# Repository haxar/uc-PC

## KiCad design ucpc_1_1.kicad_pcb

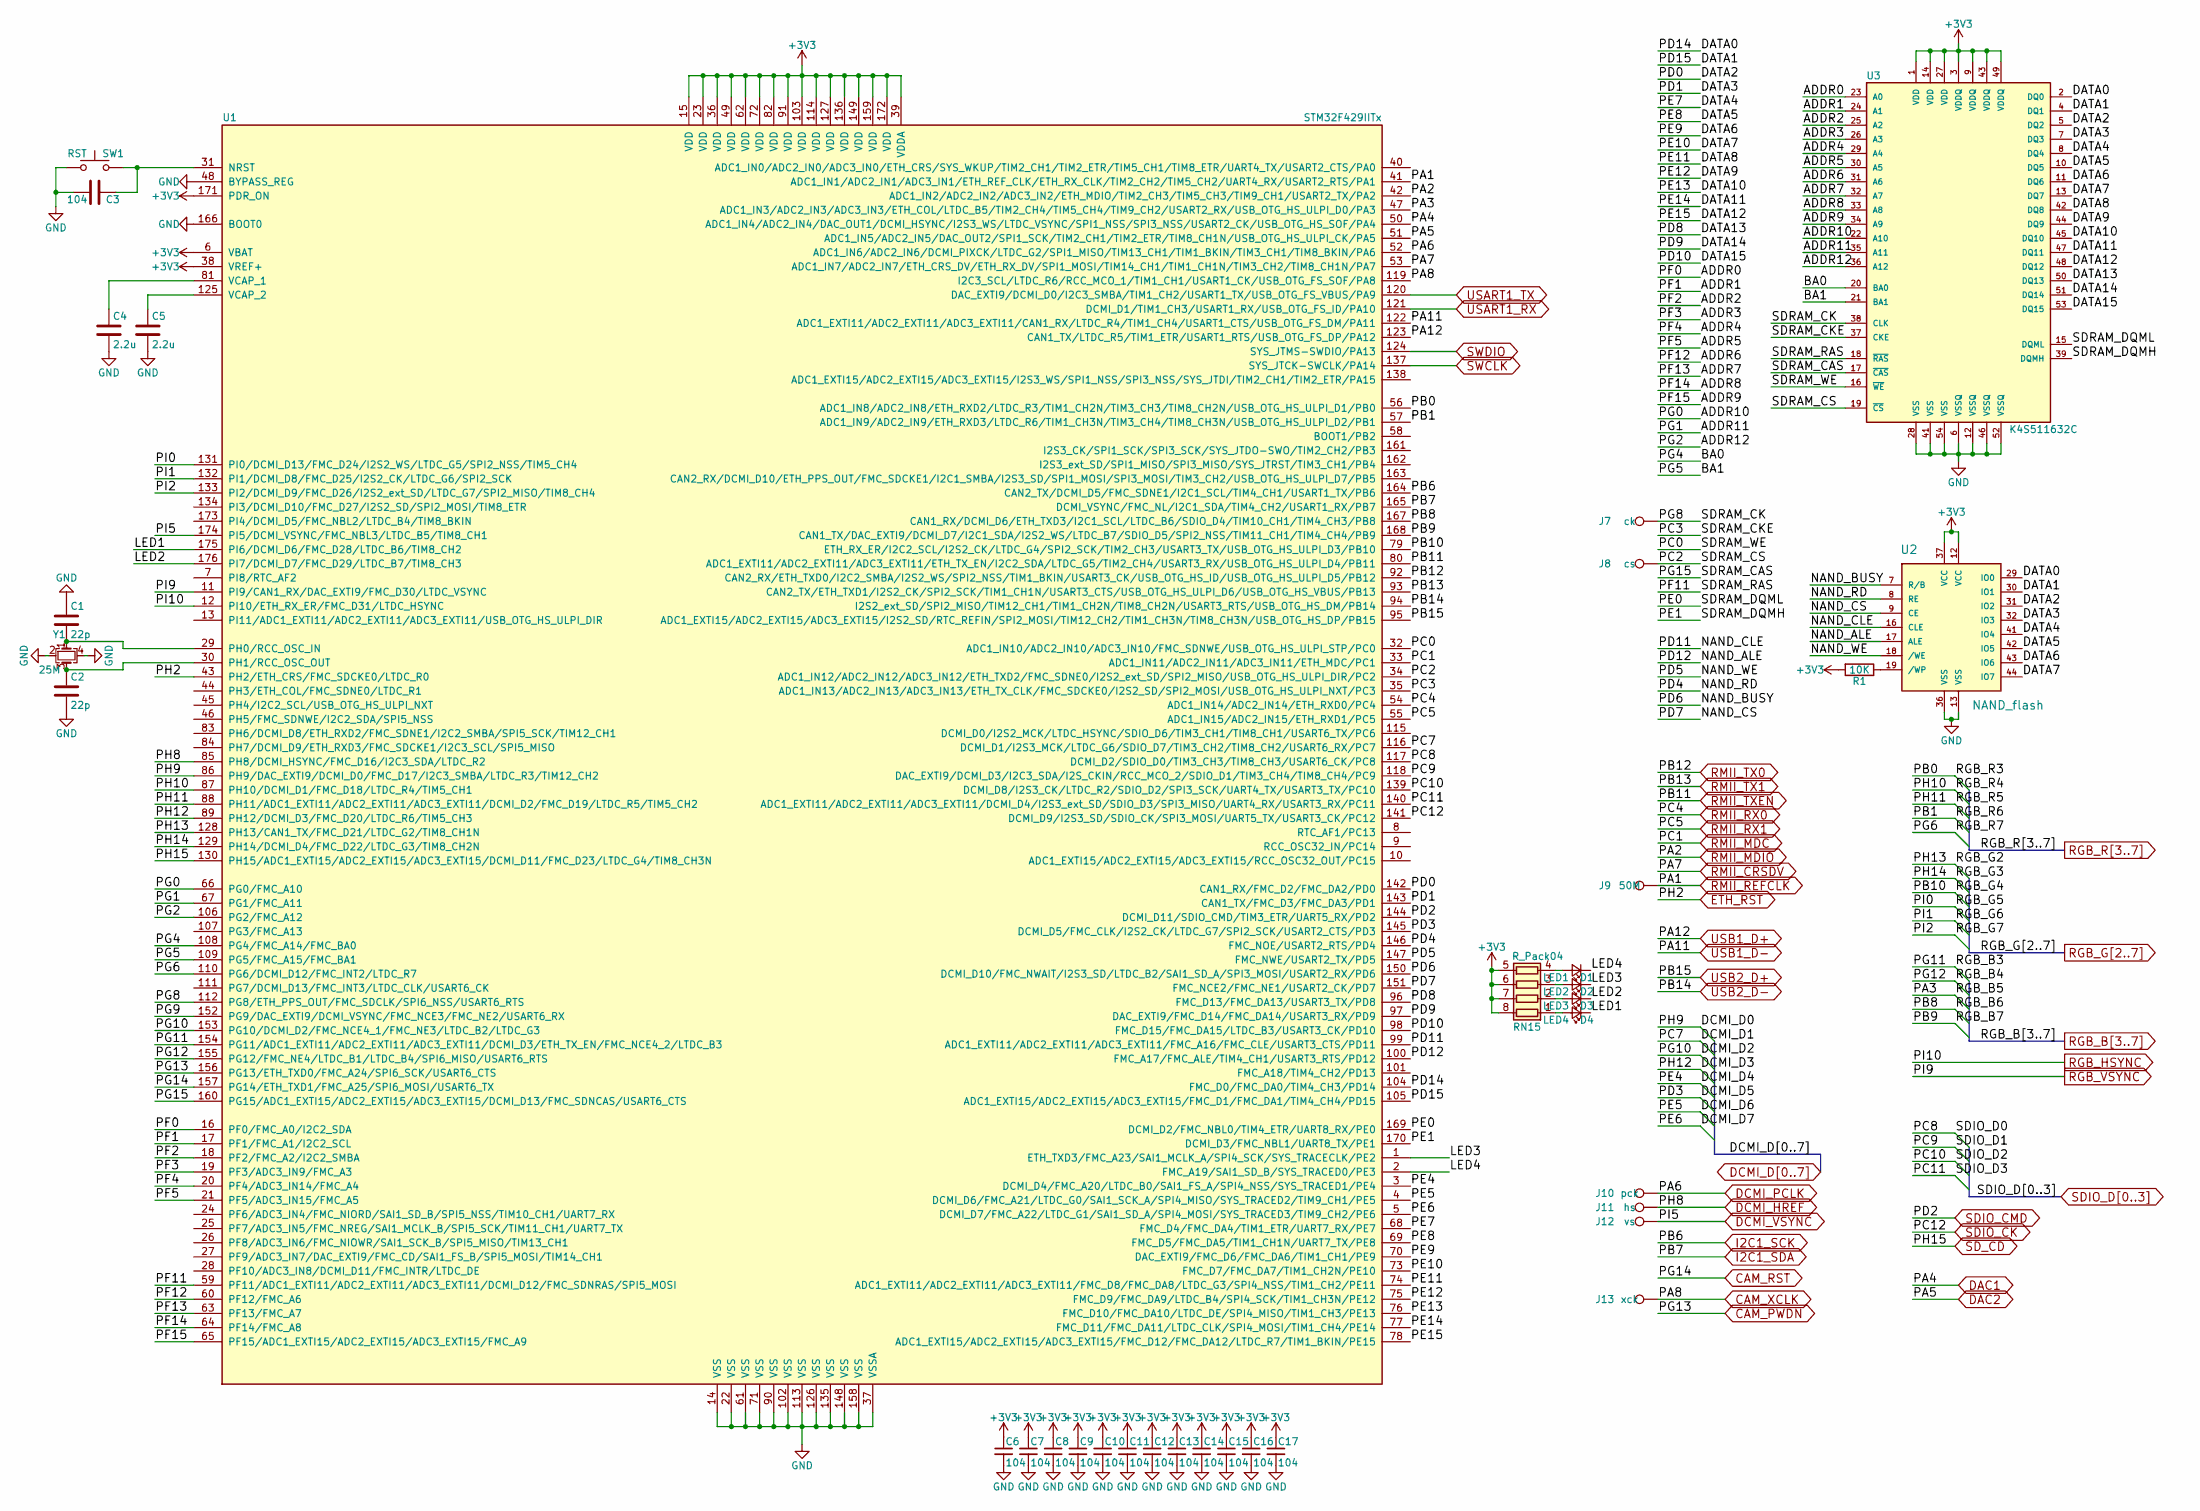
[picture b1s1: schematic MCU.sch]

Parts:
C1, C2: 22p; C_0603_1608Metric_Pad0.84x1.00mm_HandSolder
C3, C6, C7, C8, C9, C10, C11, C12, C13, C14, C15, C16, C17: 104; C_0603_1608Metric_Pad0.84x1.00mm_HandSolder
C4, C5: 2.2u; C_0603_1608Metric_Pad0.84x1.00mm_HandSolder
D1: LED1; D_0603_1608Metric_Pad0.67x1.00mm_HandSolder
D2: LED2; D_0603_1608Metric_Pad0.67x1.00mm_HandSolder
D3: LED3; D_0603_1608Metric_Pad0.67x1.00mm_HandSolder
D4: LED4; D_0603_1608Metric_Pad0.67x1.00mm_HandSolder
J7: ck; testpoint
J8: cs; testpoint
J9: 50M; testpoint
J10: pck; testpoint
J11: hs; testpoint
J12: vs; testpoint
J13: xck; testpoint
R1: 10K; R_0603_1608Metric_Pad0.84x1.00mm_HandSolder
RN15: R_Pack04; R_Array_Convex_4x0603
SW1: RST; SW_DIP_SPSTx01_Slide_6.7x4.1mm_W6.73mm_P2.54mm_LowProfile_J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
U1: STM32F429IITx; LQFP-176_24x24mm_Pitch0.5mm
U2: NAND_flash; TSSOP48
U3: K4S511632C; TSOP-54-0.8-pitch
Y1: 25M; Crystal_SMD_3225-4Pin_3.2x2.5mm

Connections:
+3V3: C6.1, C7.1, C8.1, C9.1, C10.1, C11.1, C12.1, C13.1, C14.1, C15.1, C16.1, C17.1, R1.2, RN15.5 (R4.2), RN15.6 (R3.2), RN15.7 (R2.2), RN15.8 (R1.2), U1.6 (VBAT), U1.15 (VDD), U1.23 (VDD), U1.36 (VDD), U1.38 (VREF+), U1.39 (VDDA), U1.49 (VDD), U1.62 (VDD), U1.72 (VDD), U1.82 (VDD), U1.91 (VDD), U1.103 (VDD), U1.114 (VDD), U1.127 (VDD), U1.136 (VDD), U1.149 (VDD), U1.159 (VDD), U1.171 (PDR_ON), U1.172 (VDD), U2.12 (VCC), U2.37 (VCC), U3.1 (VDD), U3.3 (VDDQ), U3.9 (VDDQ), U3.14 (VDD), U3.27 (VDD), U3.43 (VDDQ), U3.49 (VDDQ); also elsewhere on the board
/stm32f429iit6/ADDR0: U1.16 (PF0/FMC_A0/I2C2_SDA), U3.23 (A0)
/stm32f429iit6/ADDR1: U1.17 (PF1/FMC_A1/I2C2_SCL), U3.24 (A1)
/stm32f429iit6/ADDR2: U1.18 (PF2/FMC_A2/I2C2_SMBA), U3.25 (A2)
/stm32f429iit6/ADDR3: U1.19 (PF3/ADC3_IN9/FMC_A3), U3.26 (A3)
/stm32f429iit6/ADDR4: U1.20 (PF4/ADC3_IN14/FMC_A4), U3.29 (A4)
/stm32f429iit6/ADDR5: U1.21 (PF5/ADC3_IN15/FMC_A5), U3.30 (A5)
/stm32f429iit6/ADDR6: U1.60 (PF12/FMC_A6), U3.31 (A6)
/stm32f429iit6/ADDR7: U1.63 (PF13/FMC_A7), U3.32 (A7)
/stm32f429iit6/ADDR8: U1.64 (PF14/FMC_A8), U3.33 (A8)
/stm32f429iit6/ADDR9: U1.65 (PF15/ADC1_EXTI15/ADC2_EXTI15/ADC3_EXTI1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), U3.34 (A9)
/stm32f429iit6/ADDR10: U1.66 (PG0/FMC_A10), U3.22 (A10)
/stm32f429iit6/ADDR11: U1.67 (PG1/FMC_A11), U3.35 (A11)
/stm32f429iit6/ADDR12: U1.106 (PG2/FMC_A12), U3.36 (A12)
/stm32f429iit6/BA0: U1.108 (PG4/FMC_A14/FMC_BA0), U3.20 (BA0)
/stm32f429iit6/BA1: U1.109 (PG5/FMC_A15/FMC_BA1), U3.21 (BA1)
/stm32f429iit6/DATA0: U1.104 (FMC_D0/FMC_DA0/TIM4_CH3/PD14), U2.29 (IO0), U3.2 (DQ0)
/stm32f429iit6/DATA1: U1.105 (ADC1_EXTI15/ADC2_EXTI15/ADC3_EXTI15/FMC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), U2.30 (IO1), U3.4 (DQ1)
/stm32f429iit6/DATA2: U1.142 (CAN1_RX/FMC_D2/FMC_DA2/PD0), U2.31 (IO2), U3.5 (DQ2)
/stm32f429iit6/DATA3: U1.143 (CAN1_TX/FMC_D3/FMC_DA3/PD1), U2.32 (IO3), U3.7 (DQ3)
/stm32f429iit6/DATA4: U1.68 (FMC_D4/FMC_DA4/TIM1_ETR/UART7_RX/PE7), U2.41 (IO4), U3.8 (DQ4)
/stm32f429iit6/DATA5: U1.69 (FMC_D5/FMC_DA5/TIM1_CH1N/UART7_TX/PE8), U2.42 (IO5), U3.10 (DQ5)
/stm32f429iit6/DATA6: U1.70 (DAC_EXTI9/FMC_D6/FMC_DA6/TIM1_CH1/PE9), U2.43 (IO6), U3.11 (DQ6)
/stm32f429iit6/DATA7: U1.73 (FMC_D7/FMC_DA7/TIM1_CH2N/PE10), U2.44 (IO7), U3.13 (DQ7)
/stm32f429iit6/DATA8: U1.74 (ADC1_EXTI11/ADC2_EXTI11/ADC3_EXTI11/FMC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), U3.42 (DQ8)
/stm32f429iit6/DATA9: U1.75 (FMC_D9/FMC_DA9/LTDC_B4/SPI4_SCK/TIM1_CH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), U3.44 (DQ9)
/stm32f429iit6/DATA10: U1.76 (FMC_D10/FMC_DA10/LTDC_DE/SPI4_MISO/TIM1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), U3.45 (DQ10)
/stm32f429iit6/DATA11: U1.77 (FMC_D11/FMC_DA11/LTDC_CLK/SPI4_MOSI/TIM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), U3.47 (DQ11)
/stm32f429iit6/DATA12: U1.78 (ADC1_EXTI15/ADC2_EXTI15/ADC3_EXTI15/FMC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), U3.48 (DQ12)
/stm32f429iit6/DATA13: U1.96 (FMC_D13/FMC_DA13/USART3_TX/PD8), U3.50 (DQ13)
/stm32f429iit6/DATA14: U1.97 (DAC_EXTI9/FMC_D14/FMC_DA14/USART3_RX/PD9), U3.51 (DQ14)
/stm32f429iit6/DATA15: U1.98 (FMC_D15/FMC_DA15/LTDC_B3/USART3_CK/PD10), U3.53 (DQ15)
/stm32f429iit6/LED1: D4.1 (K), U1.175 (PI6/DCMI_D6/FMC_D28/LTDC_B6/TIM8_CH2)
/stm32f429iit6/LED2: D3.1 (K), U1.176 (PI7/DCMI_D7/FMC_D29/LTDC_B7/TIM8_CH3)
/stm32f429iit6/LED3: D2.1 (K), U1.1 (ETH_TXD3/FMC_A23/SAI1_MCLK_A/SPI4_SCK/S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)
/stm32f429iit6/LED4: D1.1 (K), U1.2 (FMC_A19/SAI1_SD_B/SYS_TRACED0/PE3)
/stm32f429iit6/NAND_ALE: U1.100 (FMC_A17/FMC_ALE/TIM4_CH1/USART3_RTS/PD12), U2.17 (ALE)
/stm32f429iit6/NAND_BUSY: U1.150 (DCMI_D10/FMC_NWAIT/I2S3_SD/LTDC_B2/SAI1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), U2.7 (R/B)
/stm32f429iit6/NAND_CLE: U1.99 (ADC1_EXTI11/ADC2_EXTI11/ADC3_EXTI11/FMC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), U2.16 (CLE)
/stm32f429iit6/NAND_CS: U1.151 (FMC_NCE2/FMC_NE1/USART2_CK/PD7), U2.9 (CE)
/stm32f429iit6/NAND_RD: U1.146 (FMC_NOE/USART2_RTS/PD4), U2.8 (RE)
/stm32f429iit6/NAND_WE: U1.147 (FMC_NWE/USART2_TX/PD5), U2.18 (/WE)
/stm32f429iit6/PC0: U1.32 (ADC1_IN10/ADC2_IN10/ADC3_IN10/FMC_SDNWE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), U3.16 (~WE~)
/stm32f429iit6/PC2: J8.1, U1.34 (ADC1_IN12/ADC2_IN12/ADC3_IN12/ETH_TXD2/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), U3.19 (~CS~)
/stm32f429iit6/PC3: U1.35 (ADC1_IN13/ADC2_IN13/ADC3_IN13/ETH_TX_CL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), U3.37 (CKE)
/stm32f429iit6/PE0: U1.169 (DCMI_D2/FMC_NBL0/TIM4_ETR/UART8_RX/PE0), U3.15 (DQML)
/stm32f429iit6/PE1: U1.170 (DCMI_D3/FMC_NBL1/UART8_TX/PE1), U3.39 (DQMH)
/stm32f429iit6/PF11: U1.59 (PF11/ADC1_EXTI11/ADC2_EXTI11/ADC3_EXTI1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), U3.18 (~RAS~)
/stm32f429iit6/PG8: J7.1, U1.112 (PG8/ETH_PPS_OUT/FMC_SDCLK/SPI6_NSS/USAR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), U3.38 (CLK)
/stm32f429iit6/PG9: U1.152 (PG9/DAC_EXTI9/DCMI_VSYNC/FMC_NCE3/FMC_N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)
/stm32f429iit6/PG15: U1.160 (PG15/ADC1_EXTI15/ADC2_EXTI15/ADC3_EXTI1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), U3.17 (~CAS~)
CAM_PWDN: U1.156 (PG13/ETH_TXD0/FMC_A24/SPI6_SCK/USART6_C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); also elsewhere on the board
CAM_RST: U1.157 (PG14/ETH_TXD1/FMC_A25/SPI6_MOSI/USART6_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); also elsewhere on the board
CAM_XCLK: J13.1, U1.119 (I2C3_SCL/LTDC_R6/RCC_MCO_1/TIM1_CH1/USA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); also elsewhere on the board
DAC1: U1.50 (ADC1_IN4/ADC2_IN4/DAC_OUT1/DCMI_HSYNC/I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); also elsewhere on the board
DAC2: U1.51 (ADC1_IN5/ADC2_IN5/DAC_OUT2/SPI1_SCK/TIM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); also elsewhere on the board
DCMI_D0: U1.86 (PH9/DAC_EXTI9/DCMI_D0/FMC_D17/I2C3_SMBA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); also elsewhere on the board
DCMI_D1: U1.116 (DCMI_D1/I2S3_MCK/LTDC_G6/SDIO_D7/TIM3_C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); also elsewhere on the board
DCMI_D2: U1.153 (PG10/DCMI_D2/FMC_NCE4_1/FMC_NE3/LTDC_B2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); also elsewhere on the board
DCMI_D3: U1.89 (PH12/DCMI_D3/FMC_D20/LTDC_R6/TIM5_CH3); also elsewhere on the board
DCMI_D4: U1.3 (DCMI_D4/FMC_A20/LTDC_B0/SAI1_FS_A/SPI4_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); also elsewhere on the board
DCMI_D5: U1.145 (DCMI_D5/FMC_CLK/I2S2_CK/LTDC_G7/SPI2_SC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); also elsewhere on the board
DCMI_D6: U1.4 (DCMI_D6/FMC_A21/LTDC_G0/SAI1_SCK_A/SPI4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); also elsewhere on the board
DCMI_D7: U1.5 (DCMI_D7/FMC_A22/LTDC_G1/SAI1_SD_A/SPI4_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); also elsewhere on the board
DCMI_HREF: J11.1, U1.85 (PH8/DCMI_HSYNC/FMC_D16/I2C3_SDA/LTDC_R2); also elsewhere on the board
DCMI_PCLK: J10.1, U1.52 (ADC1_IN6/ADC2_IN6/DCMI_PIXCK/LTDC_G2/SP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); also elsewhere on the board
DCMI_VSYNC: J12.1, U1.174 (PI5/DCMI_VSYNC/FMC_NBL3/LTDC_B5/TIM8_CH1); also elsewhere on the board
ETH_RST: U1.43 (PH2/ETH_CRS/FMC_SDCKE0/LTDC_R0); also elsewhere on the board
GND: C1.1, C2.2, C3.2, C4.2, C5.2, C6.2, C7.2, C8.2, C9.2, C10.2, C11.2, C12.2, C13.2, C14.2, C15.2, C16.2, C17.2, SW1.1, U1.14 (VSS), U1.22 (VSS), U1.37 (VSSA), U1.48 (BYPASS_REG), U1.61 (VSS), U1.71 (VSS), U1.90 (VSS), U1.102 (VSS), U1.113 (VSS), U1.126 (VSS), U1.135 (VSS), U1.148 (VSS), U1.158 (VSS), U1.166 (BOOT0), U2.13 (VSS), U2.36 (VSS), U3.6 (VSSQ), U3.12 (VSSQ), U3.28 (VSS), U3.41 (VSS), U3.46 (VSSQ), U3.52 (VSSQ), U3.54 (VSS), Y1.2, Y1.4; also elsewhere on the board
I2C1_SCK: U1.164 (CAN2_TX/DCMI_D5/FMC_SDNE1/I2C1_SCL/TIM4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); also elsewhere on the board
I2C1_SDA: U1.165 (DCMI_VSYNC/FMC_NL/I2C1_SDA/TIM4_CH2/USA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); also elsewhere on the board
unnamed: C1.2, U1.29 (PH0/RCC_OSC_IN), Y1.1
unnamed: C2.1, U1.30 (PH1/RCC_OSC_OUT), Y1.3
unnamed: C3.1, SW1.2, U1.31 (NRST)
unnamed: C4.1, U1.81 (VCAP_1)
unnamed: C5.1, U1.125 (VCAP_2)
unnamed: D1.2 (A), RN15.4 (R4.1)
unnamed: D2.2 (A), RN15.3 (R3.1)
unnamed: D3.2 (A), RN15.2 (R2.1)
unnamed: D4.2 (A), RN15.1 (R1.1)
unnamed: R1.1, U2.19 (/WP)
RGB_B3: U1.154 (PG11/ADC1_EXTI11/ADC2_EXTI11/ADC3_EXTI1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); also elsewhere on the board
RGB_B4: U1.155 (PG12/FMC_NE4/LTDC_B1/LTDC_B4/SPI6_MISO/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); also elsewhere on the board
RGB_B5: U1.47 (ADC1_IN3/ADC2_IN3/ADC3_IN3/ETH_COL/LTDC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); also elsewhere on the board
RGB_B6: U1.167 (CAN1_RX/DCMI_D6/ETH_TXD3/I2C1_SCL/LTDC_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); also elsewhere on the board
RGB_B7: U1.168 (CAN1_TX/DAC_EXTI9/DCMI_D7/I2C1_SDA/I2S2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); also elsewhere on the board
RGB_G2: U1.128 (PH13/CAN1_TX/FMC_D21/LTDC_G2/TIM8_CH1N); also elsewhere on the board
RGB_G3: U1.129 (PH14/DCMI_D4/FMC_D22/LTDC_G3/TIM8_CH2N); also elsewhere on the board
RGB_G4: U1.79 (ETH_RX_ER/I2C2_SCL/I2S2_CK/LTDC_G4/SPI2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); also elsewhere on the board
RGB_G5: U1.131 (PI0/DCMI_D13/FMC_D24/I2S2_WS/LTDC_G5/SP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); also elsewhere on the board
RGB_G6: U1.132 (PI1/DCMI_D8/FMC_D25/I2S2_CK/LTDC_G6/SPI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); also elsewhere on the board
RGB_G7: U1.133 (PI2/DCMI_D9/FMC_D26/I2S2_ext_SD/LTDC_G7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); also elsewhere on the board
RGB_HSYNC: U1.12 (PI10/ETH_RX_ER/FMC_D31/LTDC_HSYNC); also elsewhere on the board
RGB_R3: U1.56 (ADC1_IN8/ADC2_IN8/ETH_RXD2/LTDC_R3/TIM1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); also elsewhere on the board
RGB_R4: U1.87 (PH10/DCMI_D1/FMC_D18/LTDC_R4/TIM5_CH1); also elsewhere on the board
RGB_R5: U1.88 (PH11/ADC1_EXTI11/ADC2_EXTI11/ADC3_EXTI1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); also elsewhere on the board
RGB_R6: U1.57 (ADC1_IN9/ADC2_IN9/ETH_RXD3/LTDC_R6/TIM1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); also elsewhere on the board
RGB_R7: U1.110 (PG6/DCMI_D12/FMC_INT2/LTDC_R7); also elsewhere on the board
RGB_VSYNC: U1.11 (PI9/CAN1_RX/DAC_EXTI9/FMC_D30/LTDC_VSYNC); also elsewhere on the board
RMII_CRSDV: U1.53 (ADC1_IN7/ADC2_IN7/ETH_CRS_DV/ETH_RX_DV/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); also elsewhere on the board
RMII_MDC: U1.33 (ADC1_IN11/ADC2_IN11/ADC3_IN11/ETH_MDC/P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); also elsewhere on the board
RMII_MDIO: U1.42 (ADC1_IN2/ADC2_IN2/ADC3_IN2/ETH_MDIO/TIM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); also elsewhere on the board
RMII_REFCLK: J9.1, U1.41 (ADC1_IN1/ADC2_IN1/ADC3_IN1/ETH_REF_CLK/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); also elsewhere on the board
RMII_RX0: U1.54 (ADC1_IN14/ADC2_IN14/ETH_RXD0/PC4); also elsewhere on the board
RMII_RX1: U1.55 (ADC1_IN15/ADC2_IN15/ETH_RXD1/PC5); also elsewhere on the board
RMII_TX0: U1.92 (CAN2_RX/ETH_TXD0/I2C2_SMBA/I2S2_WS/SPI2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); also elsewhere on the board
RMII_TX1: U1.93 (CAN2_TX/ETH_TXD1/I2S2_CK/SPI2_SCK/TIM1_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); also elsewhere on the board
RMII_TXEN: U1.80 (ADC1_EXTI11/ADC2_EXTI11/ADC3_EXTI11/ETH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); also elsewhere on the board
SDIO_CK: U1.141 (DCMI_D9/I2S3_SD/SDIO_CK/SPI3_MOSI/UART5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); also elsewhere on the board
SDIO_CMD: U1.144 (DCMI_D11/SDIO_CMD/TIM3_ETR/UART5_RX/PD2); also elsewhere on the board
SDIO_D0: U1.117 (DCMI_D2/SDIO_D0/TIM3_CH3/TIM8_CH3/USART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); also elsewhere on the board
SDIO_D1: U1.118 (DAC_EXTI9/DCMI_D3/I2C3_SDA/I2S_CKIN/RCC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); also elsewhere on the board
SDIO_D2: U1.139 (DCMI_D8/I2S3_CK/LTDC_R2/SDIO_D2/SPI3_SC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); also elsewhere on the board
SDIO_D3: U1.140 (ADC1_EXTI11/ADC2_EXTI11/ADC3_EXTI11/DCM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); also elsewhere on the board
SD_CD: U1.130 (PH15/ADC1_EXTI15/ADC2_EXTI15/ADC3_EXTI1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); also elsewhere on the board
SWCLK: U1.137 (SYS_JTCK-SWCLK/PA14); also elsewhere on the board
SWDIO: U1.124 (SYS_JTMS-SWDIO/PA13); also elsewhere on the board
USART1_RX: U1.121 (DCMI_D1/TIM1_CH3/USART1_RX/USB_OTG_FS_I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); also elsewhere on the board
USART1_TX: U1.120 (DAC_EXTI9/DCMI_D0/I2C3_SMBA/TIM1_CH2/US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); also elsewhere on the board
USB1_D+: U1.123 (CAN1_TX/LTDC_R5/TIM1_ETR/USART1_RTS/USB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); also elsewhere on the board
USB1_D-: U1.122 (ADC1_EXTI11/ADC2_EXTI11/ADC3_EXTI11/CAN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); also elsewhere on the board
USB2_D+: U1.95 (ADC1_EXTI15/ADC2_EXTI15/ADC3_EXTI15/I2S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); also elsewhere on the board
USB2_D-: U1.94 (I2S2_ext_SD/SPI2_MISO/TIM12_CH1/TIM1_CH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); also elsewhere on the board

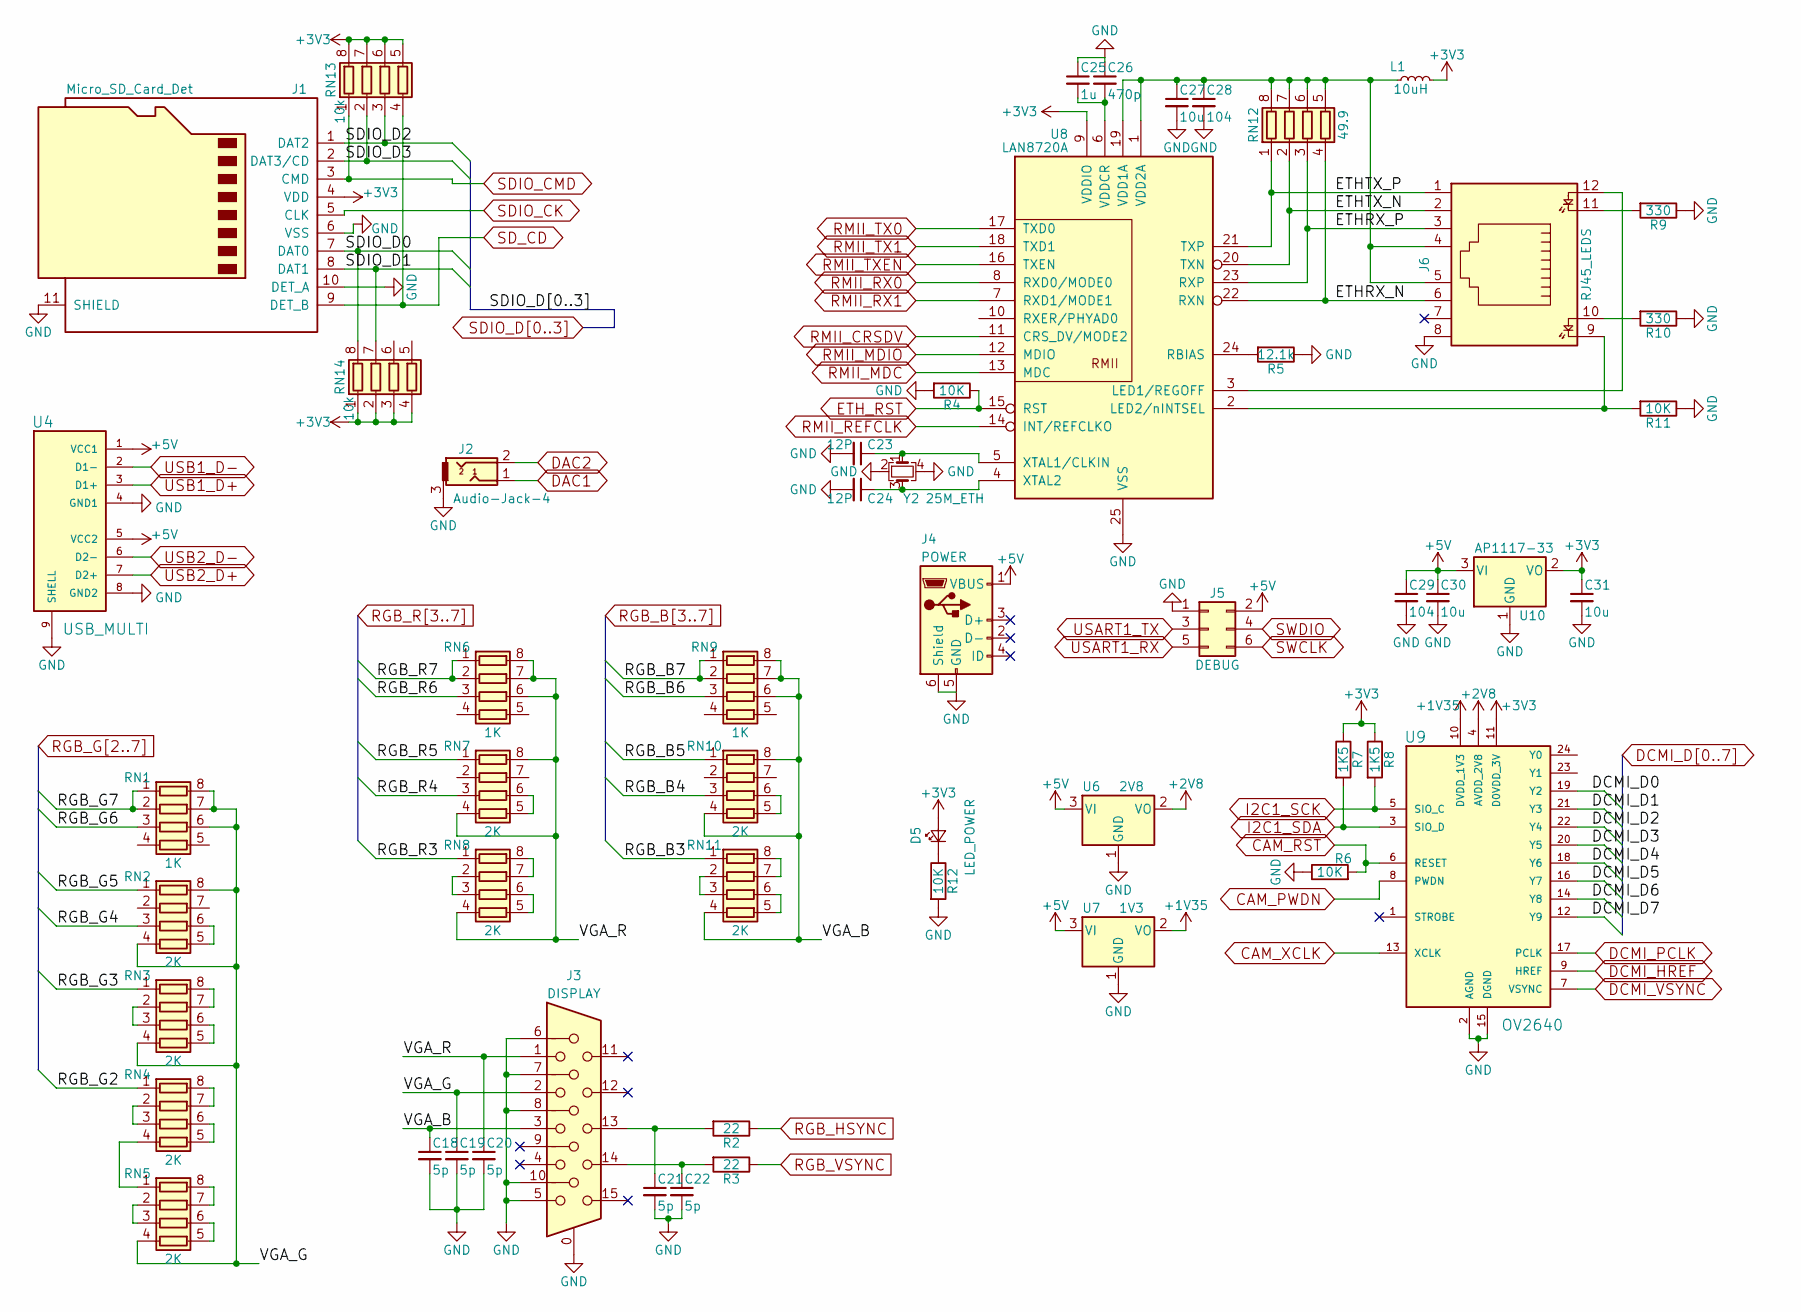
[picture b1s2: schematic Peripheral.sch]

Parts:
C18, C19, C20, C21, C22: 5p; C_0603_1608Metric_Pad0.84x1.00mm_HandSolder
C23, C24: 12P; C_0603_1608Metric_Pad0.84x1.00mm_HandSolder
C25: 1u; C_0603_1608Metric_Pad0.84x1.00mm_HandSolder
C26: 470p; C_0603_1608Metric_Pad0.84x1.00mm_HandSolder
C27: 10u; C_0603_1608Metric_Pad0.84x1.00mm_HandSolder
C28, C29: 104; C_0603_1608Metric_Pad0.84x1.00mm_HandSolder
C30, C31: 10u; C_0805_2012Metric_Pad1.15x1.50mm_HandSolder
D5: LED_POWER; D_0603_1608Metric_Pad0.67x1.00mm_HandSolder
J1: Micro_SD_Card_Det; TF_CARD_SMALL
J2: Audio-Jack-4; PJ215-3.5MM-AUDIO
J3: DISPLAY; VGA-15-3.96
J4: POWER; USB_Micro-B
J5: DEBUG; PinHeader_2x03_P2.54mm_Vertical
J6: RJ45_LEDS; HR911105A_1
L1: 10uH; L_0805_2012Metric_Pad1.15x1.50mm_HandSolder
R2, R3: 22; R_0603_1608Metric_Pad0.84x1.00mm_HandSolder
R4, R6, R11, R12: 10K; R_0603_1608Metric_Pad0.84x1.00mm_HandSolder
R5: 12.1k; R_0603_1608Metric_Pad0.84x1.00mm_HandSolder
R7, R8: 1K5; R_0603_1608Metric_Pad0.84x1.00mm_HandSolder
R9, R10: 330; R_0603_1608Metric_Pad0.84x1.00mm_HandSolder
RN1, RN6, RN9: 1K; R_Array_Convex_4x0603
RN2, RN3, RN4, RN5, RN7, RN8, RN10, RN11: 2K; R_Array_Convex_4x0603
RN12: 49.9; R_Array_Convex_4x0603
RN13, RN14: 10k; R_Array_Convex_4x0603
U4: USB_MULTI; USB_DOUBLE
U6: 2V8; SC-59_Handsoldering
U7: 1V3; SC-59_Handsoldering
U8: LAN8720A; QFN-24-1EP_4x4mm_P0.5mm_EP2.6x2.6mm
U9: OV2640; FPC-24-0.5-pitch
U10: AP1117-33; SOT-223-3_TabPin2
Y2: 25M_ETH; Crystal_SMD_3225-4Pin_3.2x2.5mm

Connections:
+1V35: U7.2 (VO), U9.10 (DVDD_1V3)
+2V8: U6.2 (VO), U9.4 (AVDD_2V8)
+3V3: C31.1, D5.2 (A), J1.4 (VDD), L1.2, R7.1, R8.1, RN13.5 (R4.2), RN13.6 (R3.2), RN13.7 (R2.2), RN13.8 (R1.2), RN14.1 (R1.1), RN14.2 (R2.1), RN14.3 (R3.1), RN14.4 (R4.1), U8.9 (VDDIO), U9.11 (D0VDD_3V), U10.2 (VO); also elsewhere on the board
+5V: C29.1, C30.1, J4.1 (VBUS), J5.2, U4.1 (VCC1), U4.5 (VCC2), U6.3 (VI), U7.3 (VI), U10.3 (VI)
/peripheral/ETHRX_N: J6.6, RN12.4 (R4.1), U8.22 (RXN)
/peripheral/ETHRX_P: J6.3, RN12.3 (R3.1), U8.23 (RXP)
/peripheral/ETHTX_N: J6.2, RN12.2 (R2.1), U8.20 (TXN)
/peripheral/ETHTX_P: J6.1, RN12.1 (R1.1), U8.21 (TXP)
/peripheral/VGA_B: C18.1, J3.3, RN9.6 (R3.2), RN9.7 (R2.2), RN9.8 (R1.2), RN10.4 (R4.1), RN10.8 (R1.2), RN11.4 (R4.1)
/peripheral/VGA_G: C19.1, J3.2, RN1.6 (R3.2), RN1.7 (R2.2), RN1.8 (R1.2), RN2.4 (R4.1), RN2.8 (R1.2), RN3.4 (R4.1), RN5.4 (R4.1)
/peripheral/VGA_R: C20.1, J3.1, RN6.6 (R3.2), RN6.7 (R2.2), RN6.8 (R1.2), RN7.4 (R4.1), RN7.8 (R1.2), RN8.4 (R4.1)
CAM_PWDN: U9.8 (PWDN); also elsewhere on the board
CAM_RST: R6.2, U9.6 (RESET); also elsewhere on the board
CAM_XCLK: U9.13 (XCLK); also elsewhere on the board
DAC1: J2.1; also elsewhere on the board
DAC2: J2.2; also elsewhere on the board
DCMI_D0: U9.19 (Y2); also elsewhere on the board
DCMI_D1: U9.21 (Y3); also elsewhere on the board
DCMI_D2: U9.22 (Y4); also elsewhere on the board
DCMI_D3: U9.20 (Y5); also elsewhere on the board
DCMI_D4: U9.18 (Y6); also elsewhere on the board
DCMI_D5: U9.16 (Y7); also elsewhere on the board
DCMI_D6: U9.14 (Y8); also elsewhere on the board
DCMI_D7: U9.12 (Y9); also elsewhere on the board
DCMI_HREF: U9.9 (HREF); also elsewhere on the board
DCMI_PCLK: U9.17 (PCLK); also elsewhere on the board
DCMI_VSYNC: U9.7 (VSYNC); also elsewhere on the board
ETH_RST: R4.1, U8.15 (RST); also elsewhere on the board
GND: C18.2, C19.2, C20.2, C21.2, C22.2, C23.2, C24.2, C25.1, C26.1, C27.2, C28.2, C29.2, C30.2, C31.2, J1.6 (VSS), J1.10 (DET_A), J1.11 (SHIELD), J2.3, J3.0, J3.5, J3.6, J3.7, J3.8, J3.10, J4.5 (GND), J4.6 (Shield), J5.1, J6.8, R4.2, R5.1, R6.1, R9.1, R10.1, R11.1, R12.2, U4.4 (GND1), U4.8 (GND2), U4.9 (SHELL), U6.1 (GND), U7.1 (GND), U8.25 (VSS), U9.2 (AGND), U9.15 (DGND), U10.1 (GND), Y2.2, Y2.4; also elsewhere on the board
I2C1_SCK: R8.2, U9.5 (SIO_C); also elsewhere on the board
I2C1_SDA: R7.2, U9.3 (SIO_D); also elsewhere on the board
unnamed: C21.1, J3.13, R2.2
unnamed: C22.1, J3.14, R3.2
unnamed: C23.1, U8.5 (XTAL1/CLKIN), Y2.1
unnamed: C24.1, U8.4 (XTAL2), Y2.3
unnamed: C25.2, C26.2, U8.6 (VDDCR)
unnamed: C27.1, C28.1, J6.4, J6.5, L1.1, RN12.5 (R4.2), RN12.6 (R3.2), RN12.7 (R2.2), RN12.8 (R1.2), U8.1 (VDD2A), U8.19 (VDD1A)
unnamed: D5.1 (K), R12.1
unnamed: J6.9, R11.2, U8.2 (LED2/nINTSEL)
unnamed: J6.10, R10.2
unnamed: J6.11, R9.2
unnamed: J6.12, U8.3 (LED1/REGOFF)
unnamed: R5.2, U8.24 (RBIAS)
unnamed: RN2.5 (R4.2), RN2.6 (R3.2)
unnamed: RN3.2 (R2.1), RN3.3 (R3.1)
unnamed: RN3.5 (R4.2), RN3.6 (R3.2)
unnamed: RN3.7 (R2.2), RN3.8 (R1.2)
unnamed: RN4.2 (R2.1), RN4.3 (R3.1)
unnamed: RN4.4 (R4.1), RN5.1 (R1.1)
unnamed: RN4.5 (R4.2), RN4.6 (R3.2)
unnamed: RN4.7 (R2.2), RN4.8 (R1.2)
unnamed: RN5.2 (R2.1), RN5.3 (R3.1)
unnamed: RN5.5 (R4.2), RN5.6 (R3.2)
unnamed: RN5.7 (R2.2), RN5.8 (R1.2)
unnamed: RN7.5 (R4.2), RN7.6 (R3.2)
unnamed: RN8.2 (R2.1), RN8.3 (R3.1)
unnamed: RN8.5 (R4.2), RN8.6 (R3.2)
unnamed: RN8.7 (R2.2), RN8.8 (R1.2)
unnamed: RN10.5 (R4.2), RN10.6 (R3.2)
unnamed: RN11.2 (R2.1), RN11.3 (R3.1)
unnamed: RN11.5 (R4.2), RN11.6 (R3.2)
unnamed: RN11.7 (R2.2), RN11.8 (R1.2)
RGB_B3: RN11.1 (R1.1); also elsewhere on the board
RGB_B4: RN10.3 (R3.1); also elsewhere on the board
RGB_B5: RN10.1 (R1.1); also elsewhere on the board
RGB_B6: RN9.3 (R3.1); also elsewhere on the board
RGB_B7: RN9.1 (R1.1), RN9.2 (R2.1); also elsewhere on the board
RGB_G2: RN4.1 (R1.1); also elsewhere on the board
RGB_G3: RN3.1 (R1.1); also elsewhere on the board
RGB_G4: RN2.3 (R3.1); also elsewhere on the board
RGB_G5: RN2.1 (R1.1); also elsewhere on the board
RGB_G6: RN1.3 (R3.1); also elsewhere on the board
RGB_G7: RN1.1 (R1.1), RN1.2 (R2.1); also elsewhere on the board
RGB_HSYNC: R2.1; also elsewhere on the board
RGB_R3: RN8.1 (R1.1); also elsewhere on the board
RGB_R4: RN7.3 (R3.1); also elsewhere on the board
RGB_R5: RN7.1 (R1.1); also elsewhere on the board
RGB_R6: RN6.3 (R3.1); also elsewhere on the board
RGB_R7: RN6.1 (R1.1), RN6.2 (R2.1); also elsewhere on the board
RGB_VSYNC: R3.1; also elsewhere on the board
RMII_CRSDV: U8.11 (CRS_DV/MODE2); also elsewhere on the board
RMII_MDC: U8.13 (MDC); also elsewhere on the board
RMII_MDIO: U8.12 (MDIO); also elsewhere on the board
RMII_REFCLK: U8.14 (INT/REFCLKO); also elsewhere on the board
RMII_RX0: U8.8 (RXD0/MODE0); also elsewhere on the board
RMII_RX1: U8.7 (RXD1/MODE1); also elsewhere on the board
RMII_TX0: U8.17 (TXD0); also elsewhere on the board
RMII_TX1: U8.18 (TXD1); also elsewhere on the board
RMII_TXEN: U8.16 (TXEN); also elsewhere on the board
SDIO_CK: J1.5 (CLK); also elsewhere on the board
SDIO_CMD: J1.3 (CMD), RN13.1 (R1.1); also elsewhere on the board
SDIO_D0: J1.7 (DAT0), RN14.8 (R1.2); also elsewhere on the board
SDIO_D1: J1.8 (DAT1), RN14.7 (R2.2); also elsewhere on the board
SDIO_D2: J1.1 (DAT2), RN13.3 (R3.1); also elsewhere on the board
SDIO_D3: J1.2 (DAT3/CD), RN13.2 (R2.1); also elsewhere on the board
SD_CD: J1.9 (DET_B), RN13.4 (R4.1); also elsewhere on the board
SWCLK: J5.6; also elsewhere on the board
SWDIO: J5.4; also elsewhere on the board
USART1_RX: J5.5; also elsewhere on the board
USART1_TX: J5.3; also elsewhere on the board
USB1_D+: U4.3 (D1+); also elsewhere on the board
USB1_D-: U4.2 (D1-); also elsewhere on the board
USB2_D+: U4.7 (D2+); also elsewhere on the board
USB2_D-: U4.6 (D2-); also elsewhere on the board

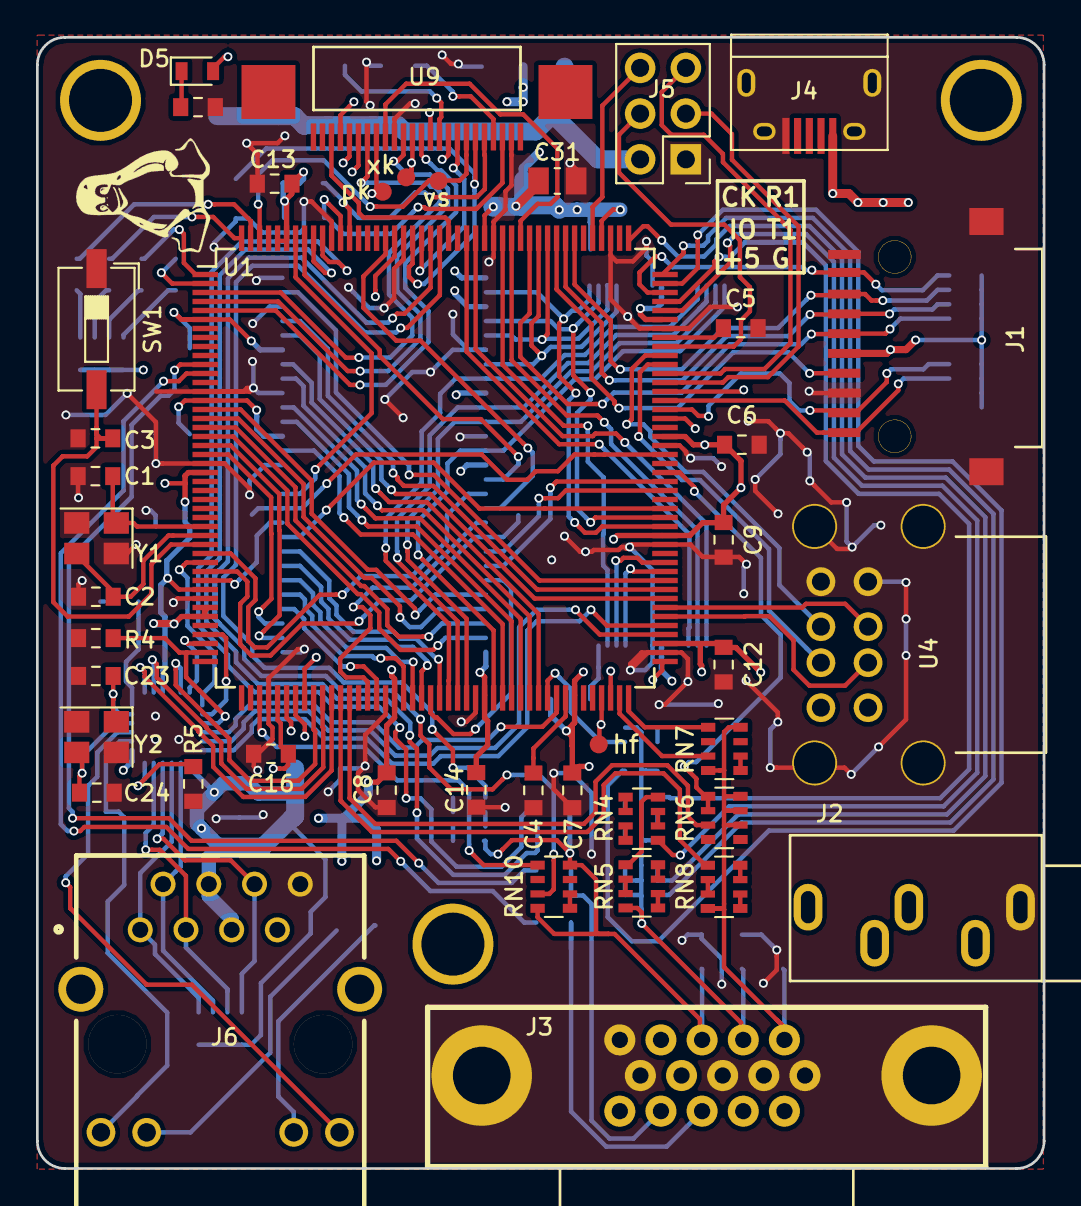
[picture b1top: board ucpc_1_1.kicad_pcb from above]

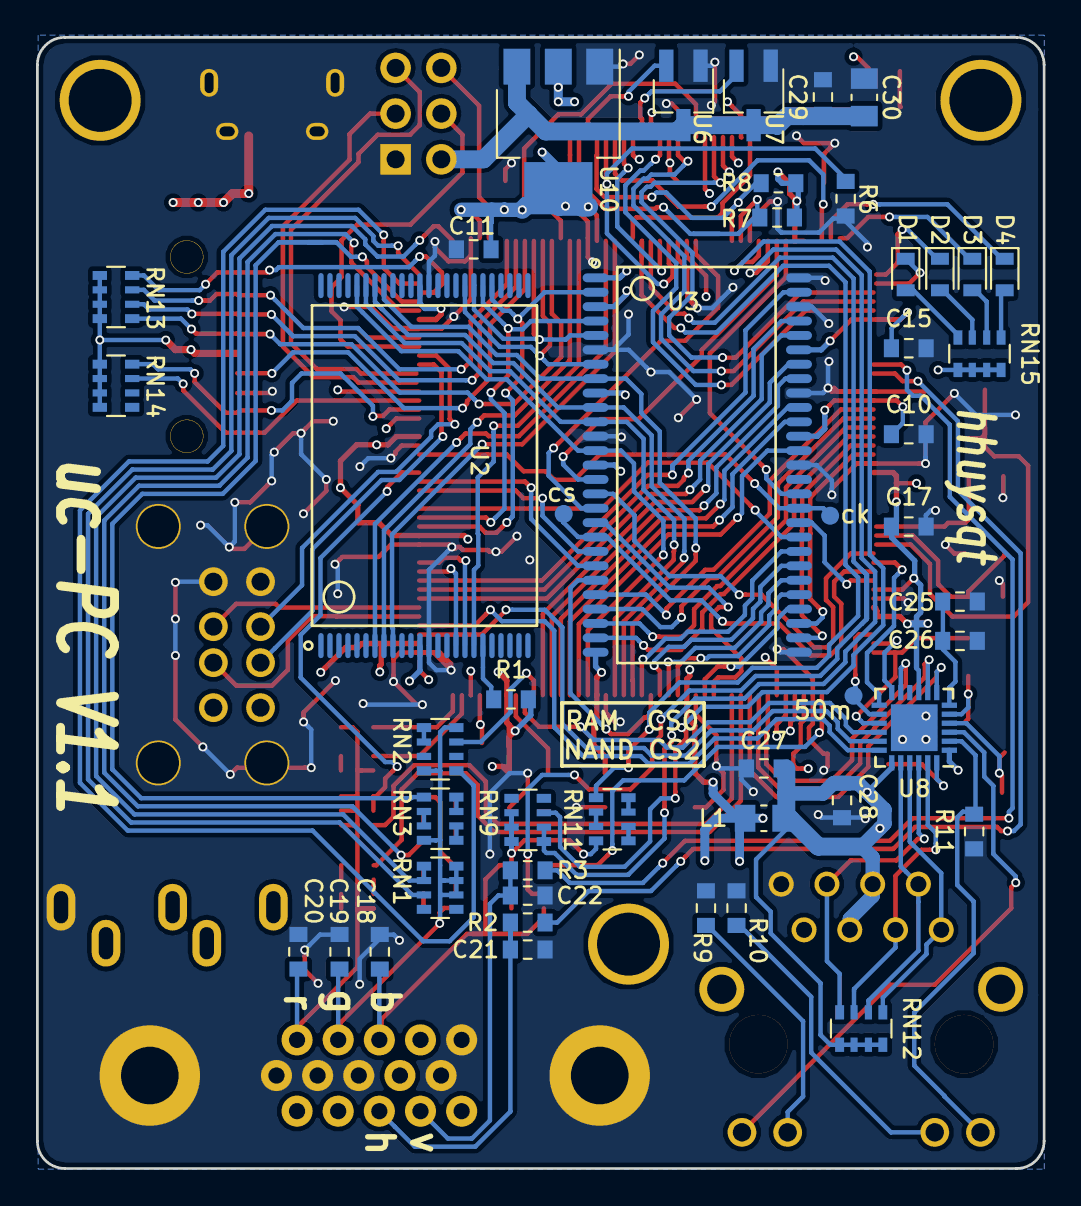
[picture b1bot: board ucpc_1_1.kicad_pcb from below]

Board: 4 copper layers, 55.9 x 62.8 mm, 89 parts (47 on the bottom side), 163 nets.

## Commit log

2022-06-06 initial import
    https://hackaday.io/project/60977-uc-pc-linux-computer-on-stm32
2022-06-06 convert to KiCad 6 format
